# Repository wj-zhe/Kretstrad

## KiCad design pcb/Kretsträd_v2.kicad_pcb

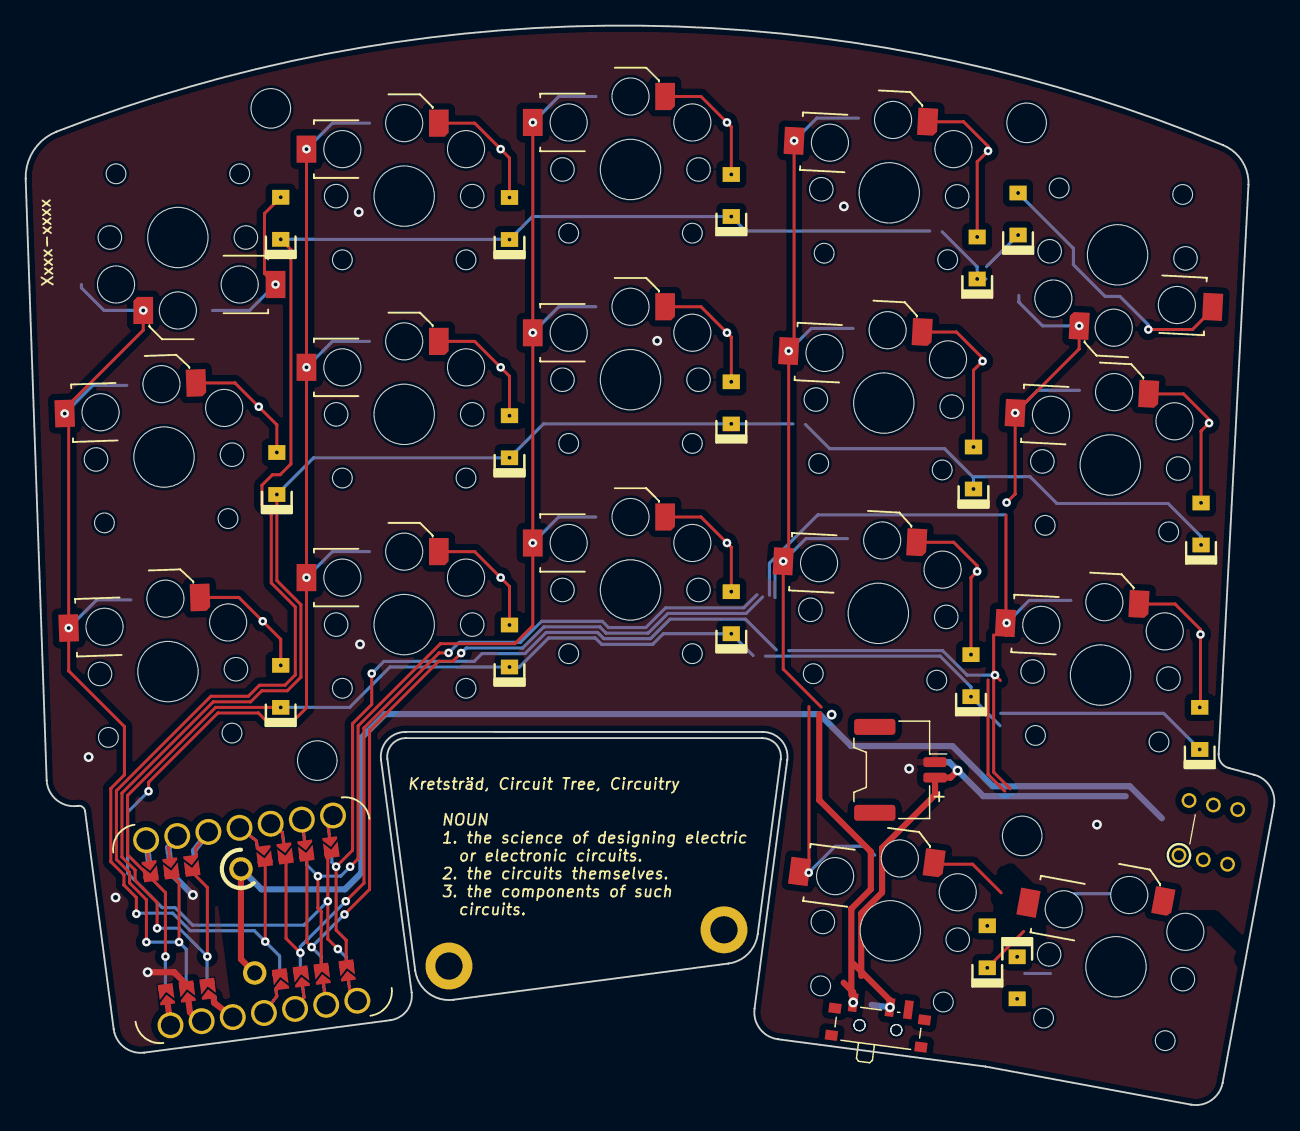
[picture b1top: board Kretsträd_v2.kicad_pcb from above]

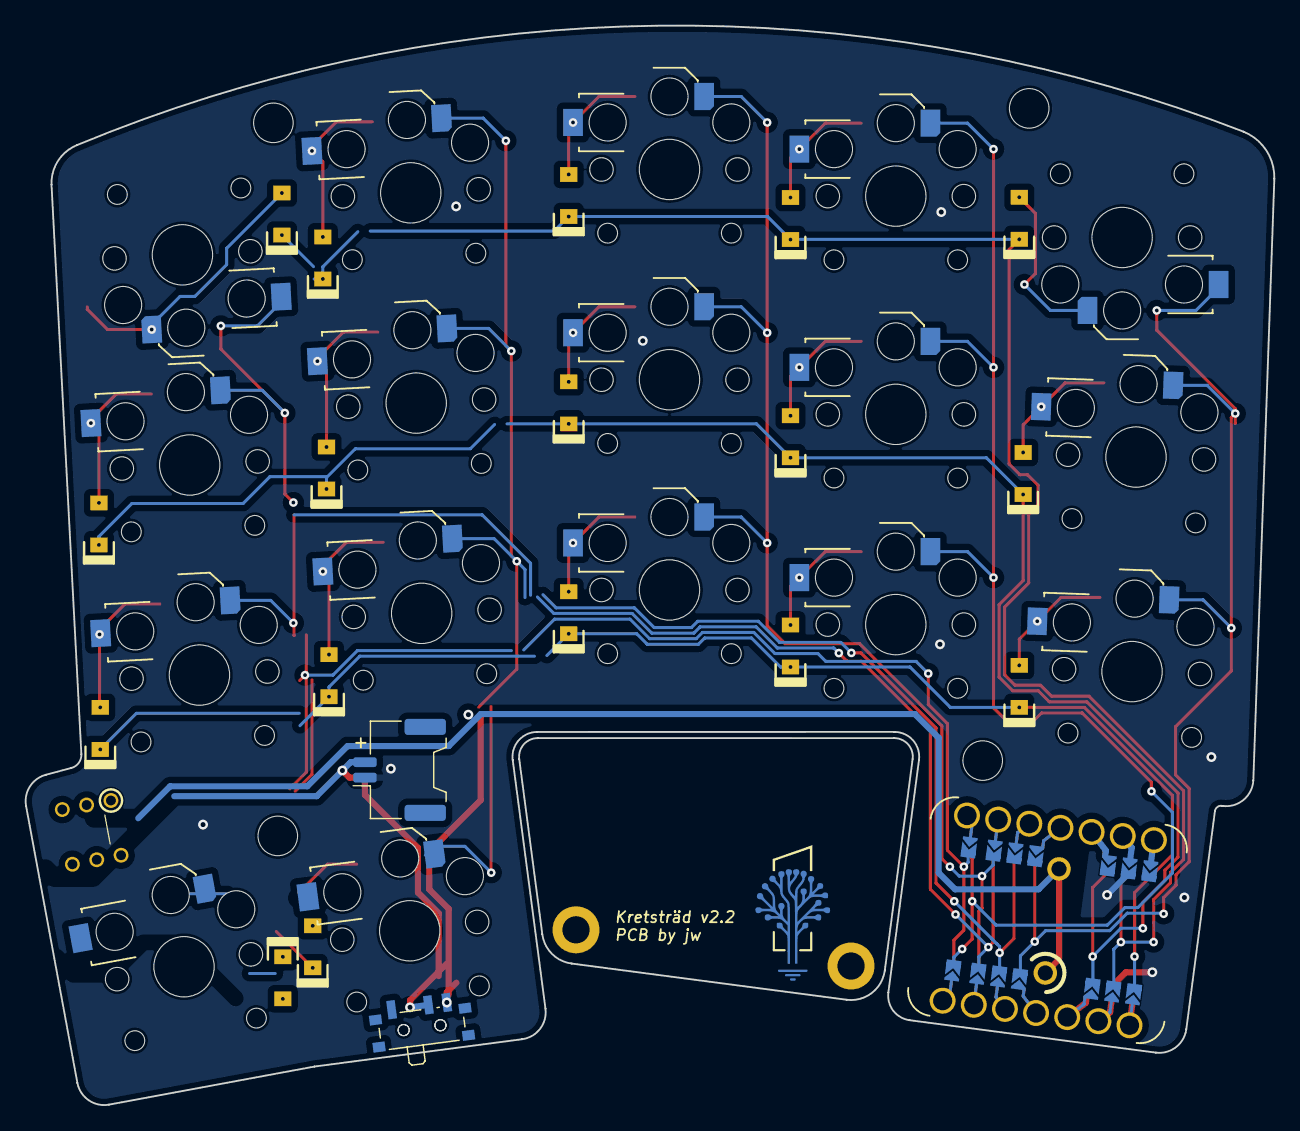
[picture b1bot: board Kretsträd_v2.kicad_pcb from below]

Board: 2 copper layers, 101.0 x 87.3 mm, 48 parts (2 on the bottom side), 29 nets.

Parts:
Batt_Hole_1, Batt_Hole_2: HOLE; MountingHole_2.2mm_M2_ISO14580_Pad
D1, D2, D3, D4, D5, D6, D7, D8, D9, D10, D11, D12, D13, D14, D15, D16, D17: D; Diode_SOD123_THT_v3
J1, J2: Conn_01x02_Female; Molex_Panelmate_53780-0270_1x02-1MP_P1.25mm_Horizontal
J3, J4: Conn_01x01_Socket; Pogopin_socket_1x01_1.20mm_vertical
PWR_SW_1, PWR_SW_2: SW_SPDT; SW_SPDT_PCM12
PWR_SW_3: SW_DPDT; Button_Switch_Push_Vertical_2P2T_Toggle_5.8x5.8
SW1: SW1; Kailh_Choc_PG1350_v1+2_Hotswap_reversible
SW2: SW2; Kailh_Choc_PG1350_v1+2_Hotswap_reversible
SW3: SW3; Kailh_Choc_PG1350_v1+2_Hotswap_reversible
SW4: SW4; Kailh_Choc_PG1350_v1+2_Hotswap_reversible
SW5: SW5; Kailh_Choc_PG1350_v1+2_Hotswap_reversible
SW6: SW6; Kailh_Choc_PG1350_v1+2_Hotswap_reversible
SW7: SW7; Kailh_Choc_PG1350_v1+2_Hotswap_reversible
SW8: SW8; Kailh_Choc_PG1350_v1+2_Hotswap_reversible
SW9: SW9; Kailh_Choc_PG1350_v1+2_Hotswap_reversible
SW10: SW10; Kailh_Choc_PG1350_v1+2_Hotswap_reversible
SW11: SW11; Kailh_Choc_PG1350_v1+2_Hotswap_reversible
SW12: SW12; Kailh_Choc_PG1350_v1+2_Hotswap_reversible
SW13: SW13; Kailh_Choc_PG1350_v1+2_Hotswap_reversible
SW14: SW14; Kailh_Choc_PG1350_v1+2_Hotswap_reversible
SW15: SW15; Kailh_Choc_PG1350_v1+2_Hotswap_reversible
SW16: SW16; Kailh_Choc_PG1350_v1+2_Hotswap_reversible
SW17: SW17; Kailh_Choc_PG1350_v1+2_Hotswap_reversible
TH1, TH2, TH3, TH4: HOLE; MountingHole_3.2mm_M3
U1: SeeeduinoXIAO_nRF52840; Xiao_nRF52840_THT_jumper_1.55mm_hole

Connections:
BAT: J3.1, J4.1, PWR_SW_1.1 (A), PWR_SW_2.3 (C), PWR_SW_3.2 (B), PWR_SW_3.5 (B)
BT+: J1.2, J2.2, PWR_SW_1.2 (B), PWR_SW_2.2 (B), PWR_SW_3.3 (C), PWR_SW_3.6 (C)
GND: J1.1, J2.1, U1.12 (GND)
unnamed: D1.2 (A), SW1.1
unnamed: D2.2 (A), SW2.2
unnamed: D3.2 (A), SW3.2
unnamed: D4.2 (A), SW4.2
unnamed: D5.2 (A), SW5.1
unnamed: D6.2 (A), SW6.2
unnamed: D7.2 (A), SW7.2
unnamed: D8.2 (A), SW8.2
unnamed: D9.2 (A), SW9.2
unnamed: D10.2 (A), SW10.2
unnamed: D11.2 (A), SW11.2
unnamed: D12.2 (A), SW12.2
unnamed: D13.2 (A), SW13.2
unnamed: D14.2 (A), SW14.2
unnamed: D15.2 (A), SW15.2
unnamed: D16.2 (A), SW16.2
unnamed: D17.2 (A), SW17.2
col0: SW1.2, SW6.1, SW11.1, U1.3 (P0.29/A3_D3)
col1: SW2.1, SW7.1, SW12.1, U1.6 (P1.11/A6_D6/TX)
col2: SW3.1, SW8.1, SW13.1, U1.8 (P1.13/A8_D8/SCK)
col3: SW4.1, SW9.1, SW14.1, SW16.1, U1.5 (P0.05/A5_D5/SCL)
col4: SW5.2, SW10.1, SW15.1, SW17.1, U1.4 (P0.04/A4_D4/SDA)
row0: D1.1 (K), D2.1 (K), D3.1 (K), D4.1 (K), D5.1 (K), U1.1 (P0.03/A1_D1)
row1: D6.1 (K), D7.1 (K), D8.1 (K), D9.1 (K), D10.1 (K), U1.2 (P0.28/A2_D2)
row2: D11.1 (K), D12.1 (K), D13.1 (K), D14.1 (K), D15.1 (K), U1.0 (P0.02/A0_D0)
row3: D16.1 (K), D17.1 (K), U1.7 (P1.12/A7_D7/RX)

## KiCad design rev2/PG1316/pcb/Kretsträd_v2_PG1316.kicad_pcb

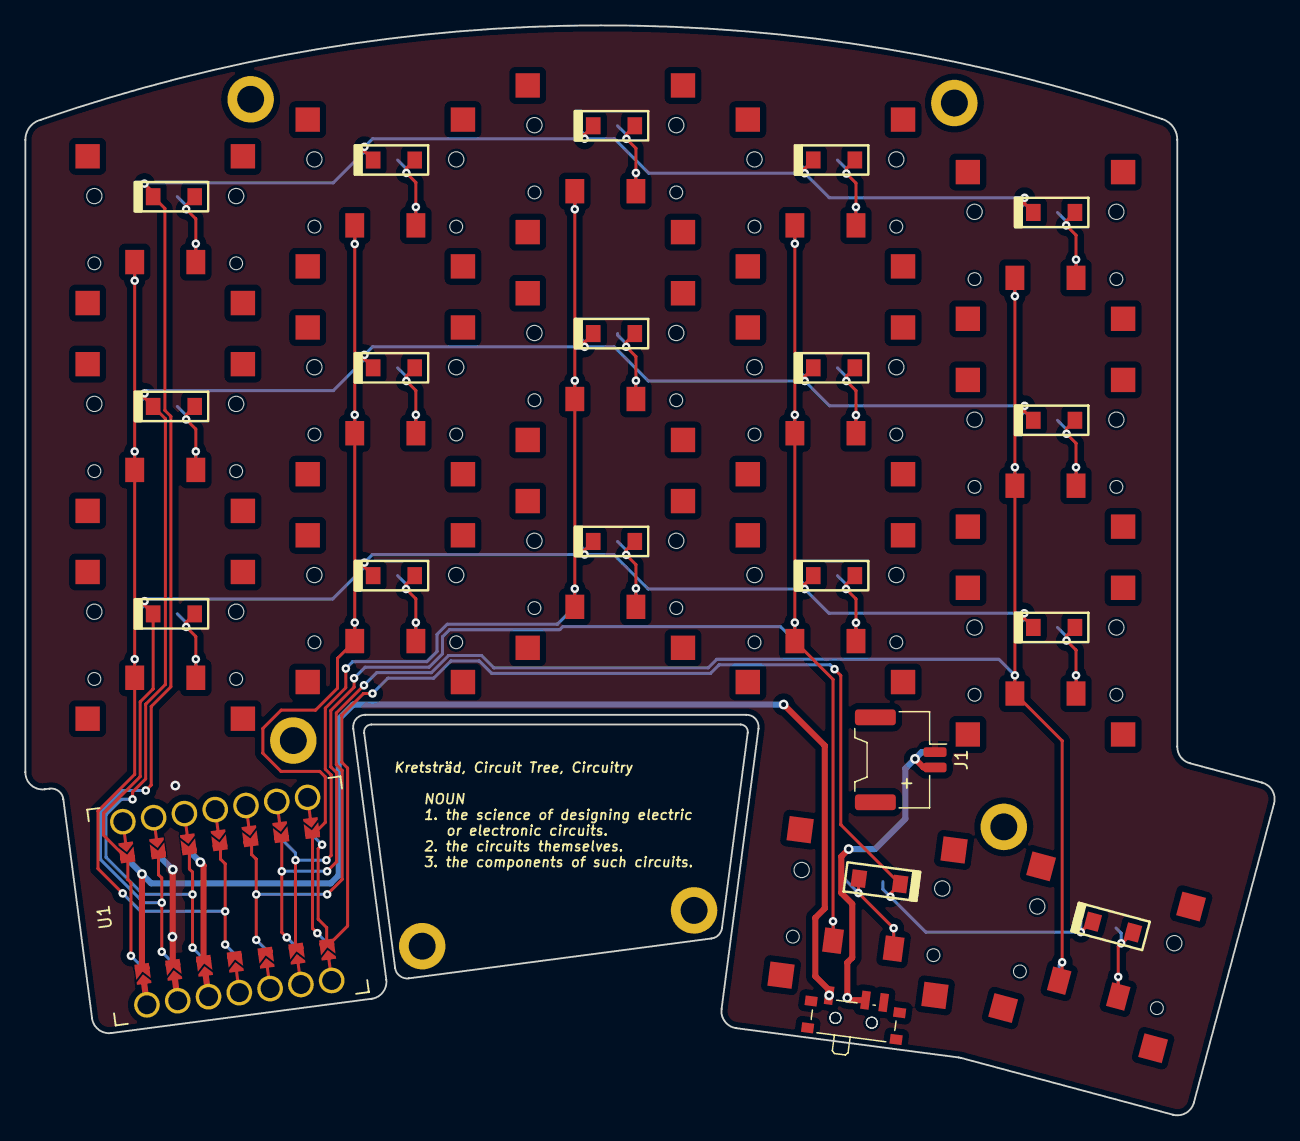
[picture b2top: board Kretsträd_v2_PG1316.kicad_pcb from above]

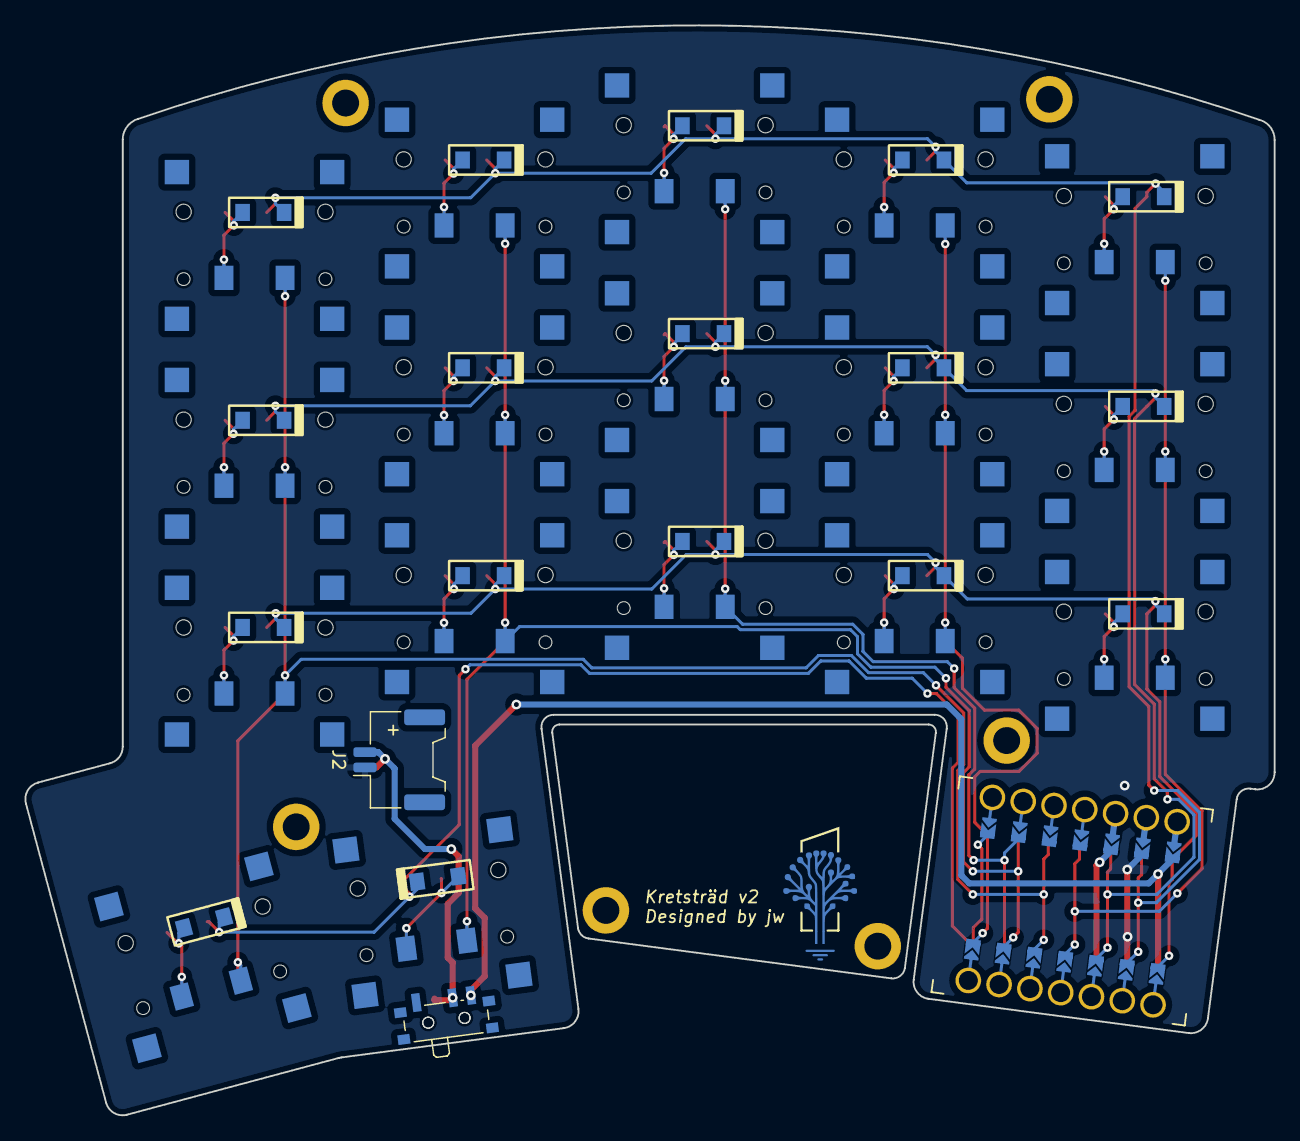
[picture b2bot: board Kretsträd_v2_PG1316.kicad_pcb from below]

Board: 2 copper layers, 102.2 x 89.2 mm, 62 parts (19 on the bottom side), 29 nets.

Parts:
Batt_Hole_1, Batt_Hole_2: HOLE; MountingHole_2.2mm_M2_ISO14580_Pad
D1, D2, D3, D4, D5, D6, D7, D8, D9, D10, D11, D12, D13, D14, D15, D16, D17: D; Diode_SOD123_SMD
Da1, Da2, Da3, Da4, Da5, Da6, Da7, Da8, Da9, Da10, Da11, Da12, Da13, Da14, Da15, Da16, Da17: D; Diode_SOD123_SMD
J1, J2: Conn_01x02_Female; Molex_Panelmate_53780-0270_1x02-1MP_P1.25mm_Horizontal
PWR_SW_1, PWR_SW_2: SW_SPDT; SW_SPDT_PCM12
SW1: SW1; Kailh_PG1316s_reversible
SW2: SW2; Kailh_PG1316s_reversible
SW3: SW3; Kailh_PG1316s_reversible
SW4: SW4; Kailh_PG1316s_reversible
SW5: SW5; Kailh_PG1316s_reversible
SW6: SW6; Kailh_PG1316s_reversible
SW7: SW7; Kailh_PG1316s_reversible
SW8: SW8; Kailh_PG1316s_reversible
SW9: SW9; Kailh_PG1316s_reversible
SW10: SW10; Kailh_PG1316s_reversible
SW11: SW11; Kailh_PG1316s_reversible
SW12: SW12; Kailh_PG1316s_reversible
SW13: SW13; Kailh_PG1316s_reversible
SW14: SW14; Kailh_PG1316s_reversible
SW15: SW15; Kailh_PG1316s_reversible
SW16: SW16; Kailh_PG1316s_reversible
SW17: SW17; Kailh_PG1316s_reversible
TH1, TH2, TH3, TH4: HOLE; MountingHole_2.2mm_M2_ISO14580_Pad
U1: SeeeduinoXIAO; Xiao THT jumper pad_hole_1.55mm

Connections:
BT+: J1.2, J2.2, PWR_SW_1.2 (B), PWR_SW_2.2 (B)
GND: J1.1, J2.1, U1.13 (GND)
unnamed: D1.2 (A), Da1.2 (A), SW1.2
unnamed: D2.2 (A), Da2.2 (A), SW2.2
unnamed: D3.2 (A), Da3.2 (A), SW3.2
unnamed: D4.2 (A), Da4.2 (A), SW4.2
unnamed: D5.2 (A), Da5.2 (A), SW5.2
unnamed: D6.2 (A), Da6.2 (A), SW6.2
unnamed: D7.2 (A), Da7.2 (A), SW7.2
unnamed: D8.2 (A), Da8.2 (A), SW8.2
unnamed: D9.2 (A), Da9.2 (A), SW9.2
unnamed: D10.2 (A), Da10.2 (A), SW10.2
unnamed: D11.2 (A), Da11.2 (A), SW11.2
unnamed: D12.2 (A), Da12.2 (A), SW12.2
unnamed: D13.2 (A), Da13.2 (A), SW13.2
unnamed: D14.2 (A), Da14.2 (A), SW14.2
unnamed: D15.2 (A), Da15.2 (A), SW15.2
unnamed: D16.2 (A), Da16.2 (A), SW16.2
unnamed: D17.2 (A), Da17.2 (A), SW17.2
RAW: PWR_SW_1.1 (A), PWR_SW_2.3 (C), U1.14 (5V)
col0: SW1.1, SW6.1, SW11.1, U1.4 (PA11_A3_D3)
col1: SW2.1, SW7.1, SW12.1, U1.7 (PB08_A6_D6_TX)
col2: SW3.1, SW8.1, SW13.1, U1.9 (PA7_A8_D8_SCK)
col3: SW4.1, SW9.1, SW14.1, SW16.1, U1.6 (PA9_A5_D5_SCL)
col4: SW5.1, SW10.1, SW15.1, SW17.1, U1.5 (PA8_A4_D4_SDA)
row0: D1.1 (K), D2.1 (K), D3.1 (K), D4.1 (K), D5.1 (K), Da1.1 (K), Da2.1 (K), Da3.1 (K), Da4.1 (K), Da5.1 (K), U1.2 (PA4_A1_D1)
row1: D6.1 (K), D7.1 (K), D8.1 (K), D9.1 (K), D10.1 (K), Da6.1 (K), Da7.1 (K), Da8.1 (K), Da9.1 (K), Da10.1 (K), U1.3 (PA10_A2_D2)
row2: D11.1 (K), D12.1 (K), D13.1 (K), D14.1 (K), D15.1 (K), Da11.1 (K), Da12.1 (K), Da13.1 (K), Da14.1 (K), Da15.1 (K), U1.1 (PA02_A0_D0)
row3: D16.1 (K), D17.1 (K), Da16.1 (K), Da17.1 (K), U1.8 (PB09_A7_D7_RX)

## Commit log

2022-06-24 Traces completely re-routed.
2022-06-24 Minor change in front silkscreen text.
2022-06-25 Tones of changes.
2022-07-04 Moved position of CR2032 battery holder, some mounting holes.
2022-07-07 1. Corrected all vias' size. 2. Minor change to circuit tree logo and text. 3. Other changes for aesthetics reasons.
2022-07-07 Included gerber files.
2022-07-07 1. Modified LIR2032 battery holder footprint. 2. Changed Molex 1.25 battery female connector location. 3. Minor changes.
2022-07-08 1. Updated switch footprint to increase solder pad size. 2. Squeezed MCU LIR2032 battery holder power switch section. 3. Re-routed a lot. 4. Reduced curvature on edge under thumb keys. 5. Removed pow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
2022-07-10 Minor changes here and there.
2022-07-13 1. Moved down col0 and col1 (out-most columns). 2. Rerouted alot to avoid 'dead zones'. 3. Added tear drops for the same reason. 4. Minor change to edge shape. 5. Other minor changes.
2022-07-14 No comment.
2022-07-14 Forgot to add tear-drops in previous commit.
2022-07-19 First PCB production.
2022-09-17 First public version.
2023-07-02 Forgot what has changed.
2024-02-12 Re-oganized last version into rev1 directory.
2024-02-12 Deleted old files.
2024-02-12 Added rev2
2024-04-05 Rev2 completely redesigned
2024-07-14 Created Kailh PG1316 based Kretsträd. 3D print case not designed.
2024-07-14 Created separated directory for choc version Kretsträd
2025-01-02 v2.1: pre-production iteration
2025-01-03 v2: pre-production: added supplementary power switches; tweaks here and there
2025-01-08 v2.1: first production
2025-05-30 v2: Modified v2 pcb, built stack-style case
2025-07-30 v2.2
2025-08-02 Reorganized directory, leaving v2.2 and making changes for v2.3
